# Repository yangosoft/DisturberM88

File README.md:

# DisturberM88
Disturb with sound. Attiny85

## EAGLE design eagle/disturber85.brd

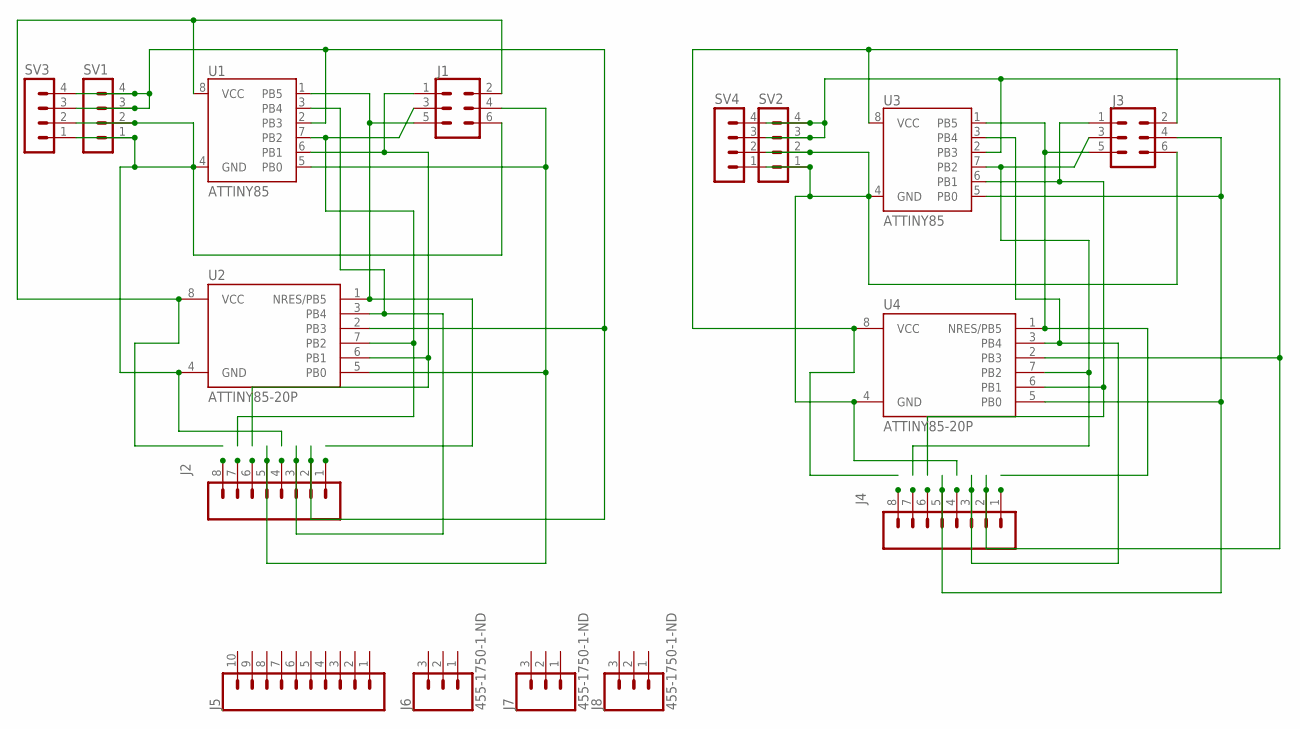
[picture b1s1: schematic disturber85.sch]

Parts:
J1, J3: CONN_03X22X3_SILK_MALE_PTH; 2X3
J2, J4: CONN_08"; 1X08
J5: CONN_10"; 1X10
J6, J7, J8: 455-1750-1-ND; 1X03
SV1, SV2, SV3, SV4: MA04-1
U1, U3: ATTINY85
U2, U4: ATTINY85-20P; PDIP08_300MIL

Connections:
unnamed: J1.6, J2.4, SV1.1, SV1.2, SV3.1, SV3.2, U1.4 (GND), U2.4 (GND)
unnamed: J1.2, J2.8, U1.8 (VCC), U2.8 (VCC)
unnamed: J1.5, J2.1, U1.1 (PB5), U2.1 (NRES/PB5)
unnamed: J1.4, J2.5, U1.5 (PB0), U2.5 (PB0)
unnamed: J1.3, J2.7, U1.7 (PB2), U2.7 (PB2)
unnamed: J1.1, J2.6, U1.6 (PB1), U2.6 (PB1)
unnamed: J2.2, SV1.3, SV1.4, SV3.3, SV3.4, U1.2 (PB3), U2.2 (PB3)
unnamed: J2.3, U1.3 (PB4), U2.3 (PB4)
unnamed: J3.6, J4.4, SV2.1, SV2.2, SV4.1, SV4.2, U3.4 (GND), U4.4 (GND)
unnamed: J3.2, J4.8, U3.8 (VCC), U4.8 (VCC)
unnamed: J3.5, J4.1, U3.1 (PB5), U4.1 (NRES/PB5)
unnamed: J3.4, J4.5, U3.5 (PB0), U4.5 (PB0)
unnamed: J3.3, J4.7, U3.7 (PB2), U4.7 (PB2)
unnamed: J3.1, J4.6, U3.6 (PB1), U4.6 (PB1)
unnamed: J4.2, SV2.3, SV2.4, SV4.3, SV4.4, U3.2 (PB3), U4.2 (PB3)
unnamed: J4.3, U3.3 (PB4), U4.3 (PB4)

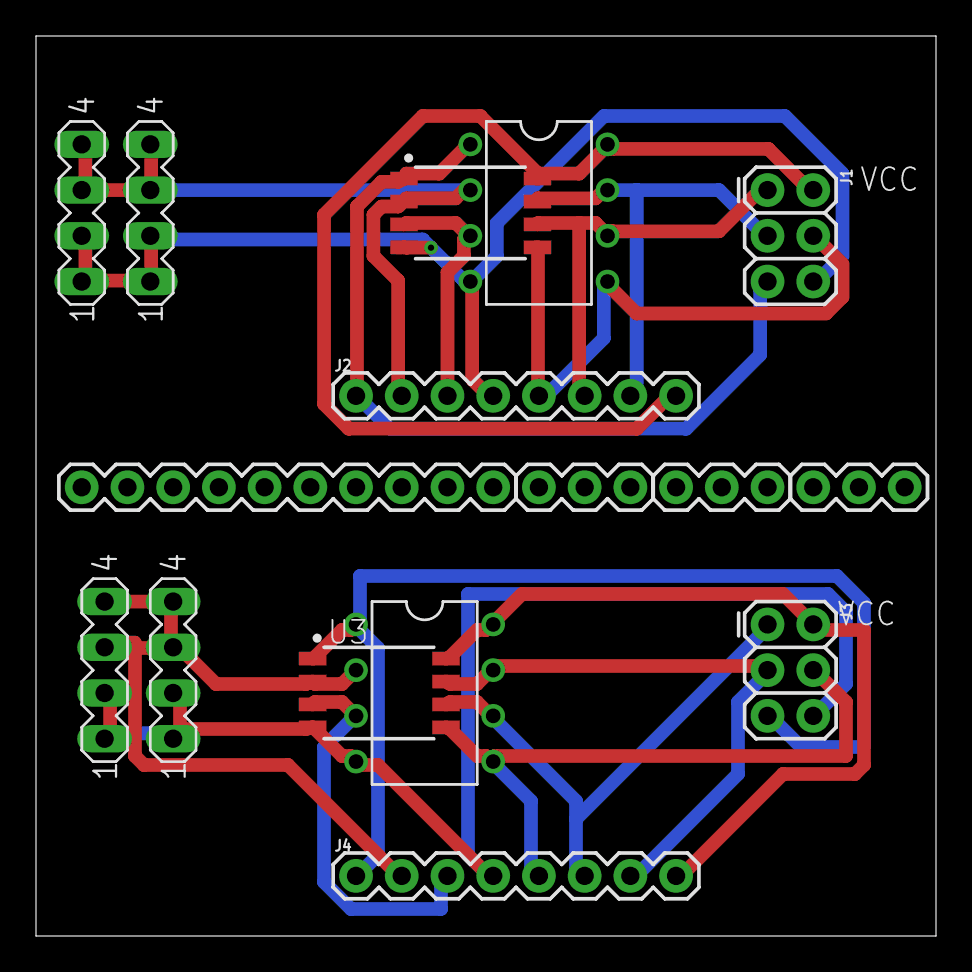
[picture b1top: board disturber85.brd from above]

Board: 2 copper layers, 50.0 x 50.0 mm, 16 parts (0 on the bottom side), 16 nets.

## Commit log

2019-08-16 Added initial src
2019-09-15 Works
2019-09-15 Added eagle
2019-09-15 Panelized
2019-09-16 Fixed makefile
2019-09-16 Added seconds since boot
2019-09-16 Changed some names to make it clearer
2019-09-17 Initial time support
2019-09-19 Added delayMs in 10ms step
2019-09-20 Added Attiny10 support
2019-09-21 Reduced size
2019-12-24 Fixed timer freq
2021-06-22 attiny13

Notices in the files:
parts and their libraries:
SparkFun-Connectors: Licensing: Creative Commons ShareAlike 4.0 International - https://creativecommons.org/licenses/by-sa/4.0
